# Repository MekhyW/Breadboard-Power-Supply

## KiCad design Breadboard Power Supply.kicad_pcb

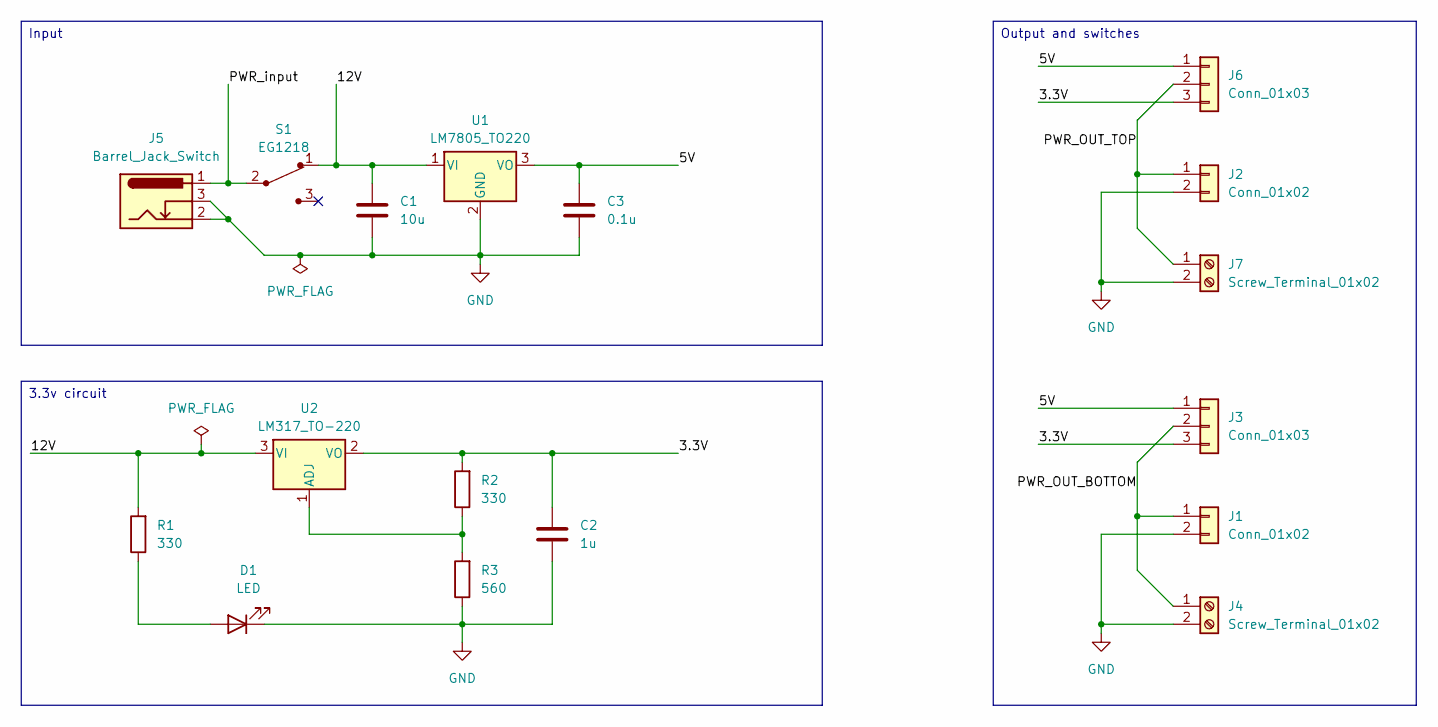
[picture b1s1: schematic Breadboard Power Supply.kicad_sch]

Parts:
C1: 10u; C_Disc_D3.0mm_W1.6mm_P2.50mm
C2: 1u; C_Disc_D3.0mm_W1.6mm_P2.50mm
C3: 0.1u; C_Disc_D3.0mm_W1.6mm_P2.50mm
D1: LED; LED_D5.0mm
J1, J2: Conn_01x02; PinHeader_1x02_P2.54mm_Vertical
J3, J6: Conn_01x03; PinHeader_1x03_P2.54mm_Vertical
J4, J7: Screw_Terminal_01x02; TerminalBlock_bornier-2_P5.08mm
J5: Barrel_Jack_Switch; BarrelJack_Horizontal
R1, R2: 330; R_Axial_DIN0204_L3.6mm_D1.6mm_P7.62mm_Horizontal
R3: 560; R_Axial_DIN0204_L3.6mm_D1.6mm_P7.62mm_Horizontal
S1: EG1218; Switch_Slide_11.6x4mm_EG1218; MPN EG1218; Digi-Key_PN EG1903-ND
U1: LM7805_TO220; TO-220-3_Vertical
U2: LM317_TO-220; TO-220-3_Vertical

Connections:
/3.3V: C2.1, J3.3, J6.3, R2.2, U2.2 (VO)
/5V: C3.1, J3.1, J6.1, U1.3 (VO)
/12V: C1.1, R1.2, S1.1, U1.1 (VI), U2.3 (VI)
/PWR_OUT_BOTTOM: J1.1, J3.2, J4.1
/PWR_OUT_TOP: J2.1, J6.2, J7.1
/PWR_input: J5.1, S1.2
GND: C1.2, C2.2, C3.2, D1.1 (K), J1.2, J2.2, J4.2, J5.2, J5.3, J7.2, R3.1, U1.2 (GND)
unnamed: D1.2 (A), R1.1
unnamed: R2.1, R3.2, U2.1 (ADJ)

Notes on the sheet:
Output and switches
3.3v circuit
Input

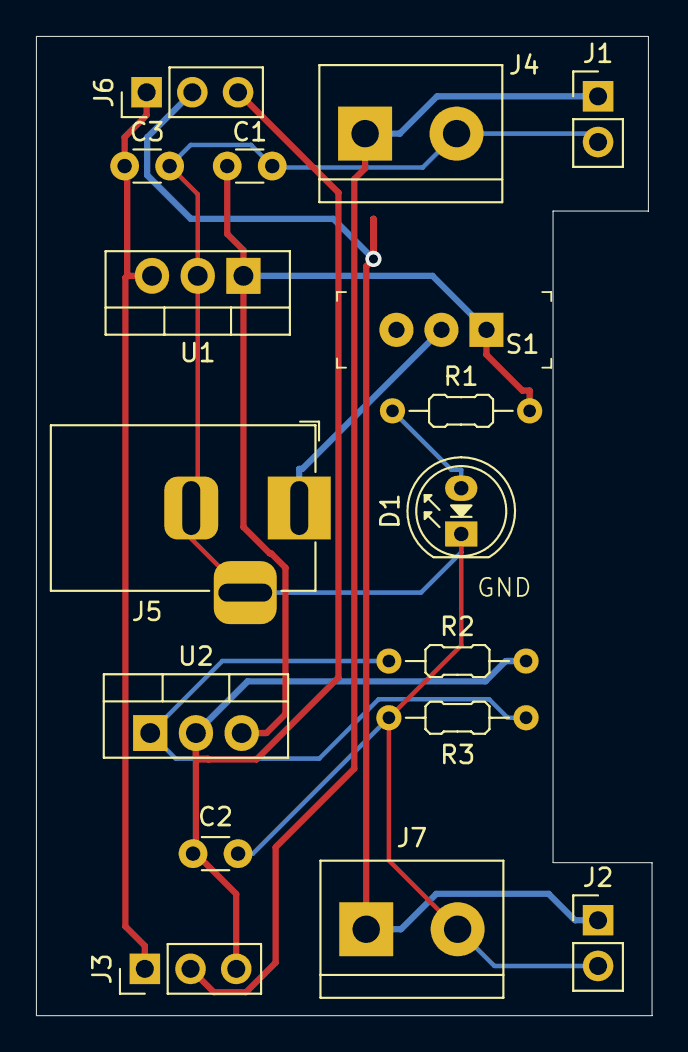
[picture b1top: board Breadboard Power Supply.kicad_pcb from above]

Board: 2 copper layers, 34.2 x 54.4 mm, 17 parts (0 on the bottom side), 9 nets.

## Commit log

2025-04-28 spawn project
2025-04-28 symbols + migrated to 9.0
2025-04-28 footprints
2025-04-29 schematic + placing
2025-04-29 fix short circuit pwr_output
2025-04-29 gerber
2025-04-29 outputdirectory
